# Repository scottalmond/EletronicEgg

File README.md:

# EletronicEgg
No-mess eletronic solution to the classical egg drop contest

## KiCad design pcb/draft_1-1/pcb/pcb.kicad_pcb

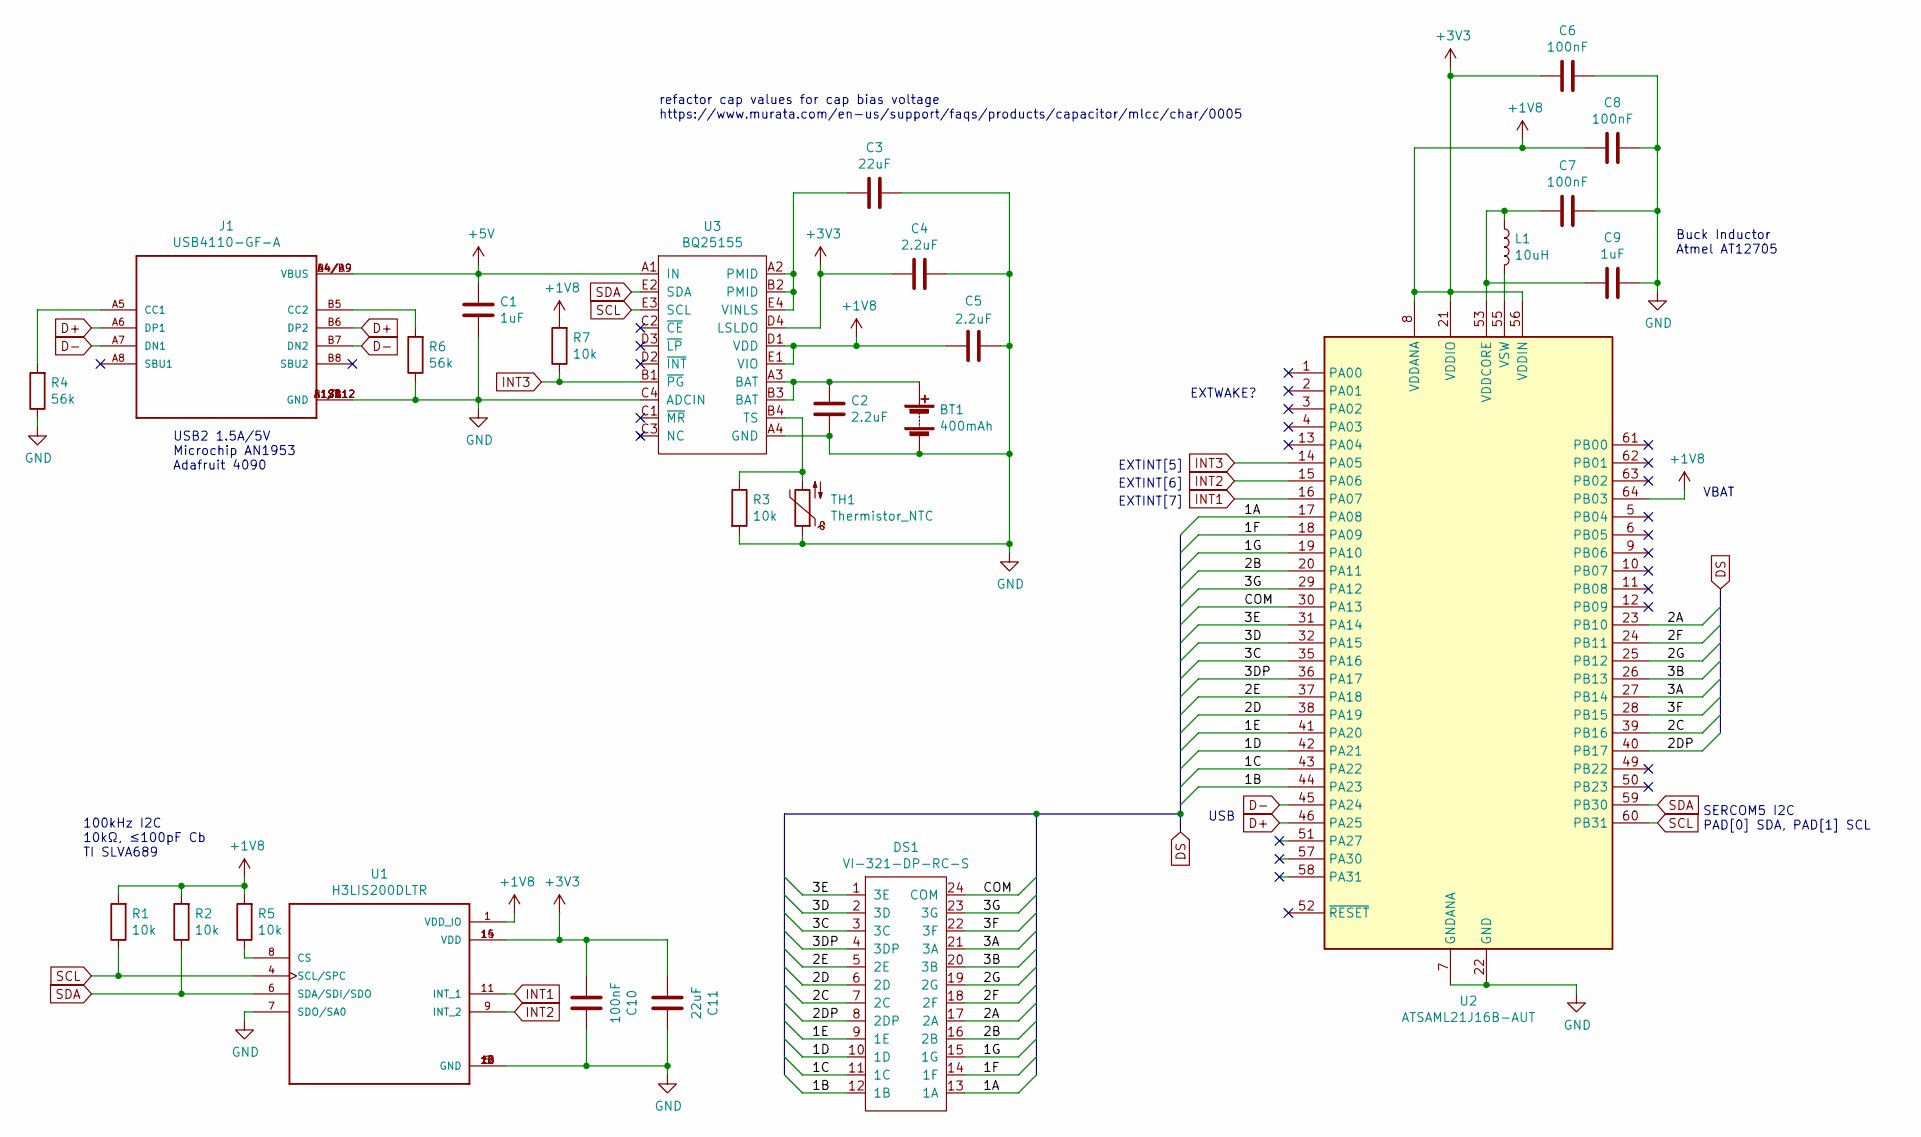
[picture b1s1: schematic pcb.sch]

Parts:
BT1: 400mAh; PinHeader_1x02_P2.54mm_Vertical
C1, C9: 1uF; C_0402_1005Metric
C2, C4, C5: 2.2uF; C_0402_1005Metric
C3, C11: 22uF; C_0805_2012Metric
C6, C7, C8, C10: 100nF; C_0402_1005Metric
DS1: VI-321-DP-RC-S
J1: USB4110-GF-A; GCT_USB4110-GF-A
L1: 10uH; L_0805_2012Metric
R1, R2, R3, R5, R7: 10k; R_0402_1005Metric
R4, R6: 56k; R_0402_1005Metric
TH1: Thermistor_NTC; R_0402_1005Metric
U1: H3LIS200DLTR; PQFN50P300X300X100-16N
U2: ATSAML21J16B-AUT; TQFP-64_10x10mm_P0.5mm
U3: BQ25155; BGA20C40P4X5_162X202X50

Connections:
+1V8: C4.1, C5.1, C6.1, C8.1, C10.2, C11.2, R1.2, R2.2, R5.2, R7.2, U1.1 (VDD_IO), U1.14 (VDD), U1.15 (VDD), U2.8 (VDDANA), U2.21 (VDDIO), U2.34 (VDDIO), U2.48 (VDDIO), U2.56 (VDDIN), U2.64 (PB03), U3.D1 (VDD), U3.D4 (LSLDO), U3.E1 (VIO)
+5V: C1.1, J1.A4/B9 (VBUS), J1.B4/A9 (VBUS), U3.A1 (IN)
/1A: DS1.13 (1A), U2.17 (PA08)
/1B: DS1.12 (1B), U2.44 (PA23)
/1C: DS1.11 (1C), U2.43 (PA22)
/1D: DS1.10 (1D), U2.42 (PA21)
/1E: DS1.9 (1E), U2.41 (PA20)
/1F: DS1.14 (1F), U2.18 (PA09)
/1G: DS1.15 (1G), U2.19 (PA10)
/2A: DS1.17 (2A), U2.23 (PB10)
/2B: DS1.16 (2B), U2.20 (PA11)
/2C: DS1.7 (2C), U2.39 (PB16)
/2D: DS1.6 (2D), U2.38 (PA19)
/2DP: DS1.8 (2DP), U2.40 (PB17)
/2E: DS1.5 (2E), U2.37 (PA18)
/2F: DS1.18 (2F), U2.24 (PB11)
/2G: DS1.19 (2G), U2.25 (PB12)
/3A: DS1.21 (3A), U2.27 (PB14)
/3B: DS1.20 (3B), U2.26 (PB13)
/3C: DS1.3 (3C), U2.35 (PA16)
/3D: DS1.2 (3D), U2.32 (PA15)
/3DP: DS1.4 (3DP), U2.36 (PA17)
/3E: DS1.1 (3E), U2.31 (PA14)
/3F: DS1.22 (3F), U2.28 (PB15)
/3G: DS1.23 (3G), U2.29 (PA12)
/COM: DS1.24 (COM), U2.30 (PA13)
D+: J1.A6 (DP1), J1.B6 (DP2), U2.46 (PA25)
D-: J1.A7 (DN1), J1.B7 (DN2), U2.45 (PA24)
GND: BT1.2 (-), C1.2, C2.2, C3.1, C4.2, C5.2, C6.2, C7.2, C8.2, C9.2, C10.1, C11.1, J1.A1/B12 (GND), J1.B1/A12 (GND), J1.S1 (GND), J1.S2 (GND), J1.S3 (GND), J1.S4 (GND), R3.2, R4.1, R6.1, TH1.1, U1.5 (GND), U1.7 (SDO/SA0), U1.10 (GND), U1.12 (GND), U1.13 (GND), U1.16 (GND), U2.7 (GNDANA), U2.22 (GND), U2.33 (GND), U2.47 (GND), U2.54 (GND), U3.A4 (GND), U3.C4 (ADCIN)
INT1: U1.11 (INT_1), U2.16 (PA07)
INT2: U1.9 (INT_2), U2.15 (PA06)
INT3: R7.1, U2.14 (PA05), U3.B1 (~PG)
unnamed: BT1.1 (+), C2.1, U3.A3 (BAT), U3.B3 (BAT)
unnamed: C3.2, U3.A2 (PMID), U3.B2 (PMID), U3.E4 (VINLS)
unnamed: C7.1, C9.1, L1.1, U2.53 (VDDCORE)
unnamed: J1.A5 (CC1), R4.2
unnamed: J1.B5 (CC2), R6.2
unnamed: L1.2, U2.55 (VSW)
unnamed: R3.1, TH1.2, U3.B4 (TS)
unnamed: R5.1, U1.8 (CS)
SCL: R1.1, U1.4 (SCL/SPC), U2.60 (PB31), U3.E3 (SCL)
SDA: R2.1, U1.6 (SDA/SDI/SDO), U2.59 (PB30), U3.E2 (SDA)

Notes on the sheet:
refactor cap values for cap bias voltage https://www.murata.com/en-us/support/faqs/products/capacitor/mlcc/char/0005
USB2 1.5A/5V Microchip AN1953 Adafruit 4090
USB
SERCOM5 I2C PAD[0] SDA, PAD[1] SCL
EXTINT[5]
EXTINT[6]
EXTINT[7]
100kHz I2C 10kΩ, ≤100pF Cb TI SLVA689
EXTWAKE?
VBAT
Buck Inductor Atmel AT12705

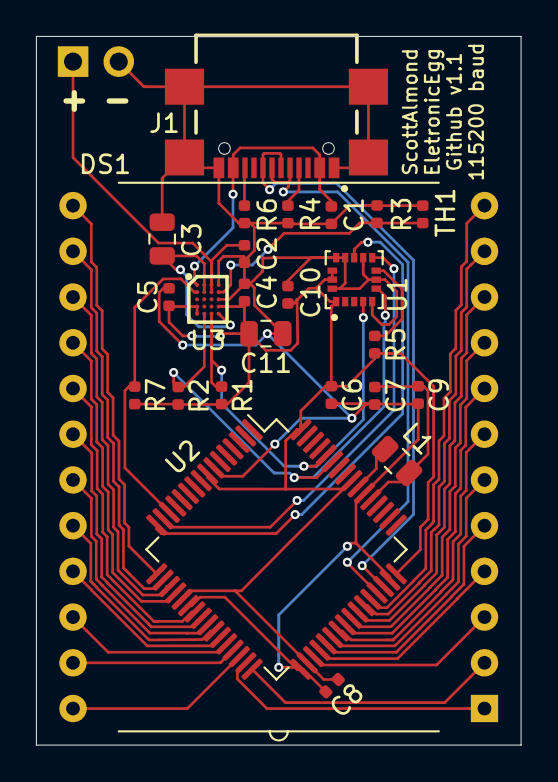
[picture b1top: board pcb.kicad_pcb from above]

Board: 2 copper layers, 26.9 x 39.4 mm, 26 parts (1 on the bottom side), 42 nets.

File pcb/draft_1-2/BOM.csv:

System Qty:,25,,,,,,,,,Price/quantity,,,,,,,,,,,,price per,,,,,,,,,ext price,,,,,,,,
Cost/System,$36.78,,,,,,,,,,,,,,,,,,,,,,,,,,,,,,,,,,,,,,
,,,,,,,,,,,,,,,,,,,,,,,,,,,,,,,,,,,,,,,
Description,Name,Pad,Component Qty/System,Component Qty to Order,Link,Alternate Link,,,,1,5,10,25,50,100,500,1000,,,,,1,5,10,25,50,100,500,1000,,1,5,10,25,50,100,500,1000,best value
400 mAh Battery,PRT-13851,BT1,1,25,https://www.digikey.com/product-detail/en/sparkfun-electroni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,https://www.sparkfun.com/products/13851,,,,4.95,,,,,,,,,,,25,4.95,4.95,4.95,4.95,4.95,4.95,4.95,4.95,,4.95,4.95,4.95,4.95,9.9,19.8,99,198,4.95
3 segment screen,VI-321-DP-RC-S,DS1,1,25,https://www.digikey.com/product-detail/en/varitronix/VI-321-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,,,,,6.3,,5.25,,,3.68,3.045,2.793,,,,25,6.3,6.3,5.25,5.25,5.25,3.68,3.045,2.793,,6.3,6.3,5.25,5.25,10.5,14.72,60.9,111.72,5.25
USB header,USB4110-GF-A,J1,1,10,https://www.digikey.com/product-detail/en/gct/USB4110-GF-A/2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,,,,,1.37,,1.25,1.69,1.12,1.067,0.88936,,,,,25,1.37,1.37,1.25,1.69,1.12,1.067,0.88936,0.88936,,1.37,1.37,1.25,1.69,2.24,4.268,17.7872,35.5744,1.25
200g accel,H3LIS200DLTR,U1,1,25,https://www.digikey.com/product-detail/en/stmicroelectronics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,,,,,7.34,,6.63,6.34,,5.49,4.78252,4.16543,,,,25,7.34,7.34,6.63,6.34,6.34,5.49,4.78252,4.16543,,7.34,7.34,6.63,6.34,12.68,21.96,95.6504,166.6172,6.34
SAML21J,ATSAML21J16B-AUT,U2,1,25,https://www.digikey.com/product-detail/en/microchip-technolo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,,,,,3.32,,,3.02,,2.73,,,,,,25,3.32,3.32,3.32,3.02,3.02,2.73,2.73,2.73,,3.32,3.32,3.32,3.02,6.04,10.92,54.6,109.2,3.02
PMIC/LDO,BQ25155YFPT,U3,1,25,https://www.digikey.com/product-detail/en/texas-instruments/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,,,,,3.31,,2.98,2.81,,2.31,,,,,,25,3.31,3.31,2.98,2.81,2.81,2.31,2.31,2.31,,3.31,3.31,2.98,2.81,5.62,9.24,46.2,92.4,2.81
1 uF 0805,CC0805KKX7R7BB105,"C1,C9",2,100,https://www.digikey.com/product-detail/en/yageo/CC0805KKX7R7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,,,,,0.18,,0.13,,,0.0611,,0.03544,,,,50,0.18,0.18,0.13,0.13,0.13,0.0611,0.0611,0.03544,,0.36,0.36,0.26,0.26,0.26,0.2444,1.222,1.4176,0.2444
2.2uF 0805,GCM21BR71E225KA73L,C2,1,25,https://www.digikey.com/product-detail/en/murata-electronics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,,,,,0.64,,0.453,,,0.298,0.22076,0.18764,,,,25,0.64,0.64,0.453,0.453,0.453,0.298,0.22076,0.18764,,0.64,0.64,0.453,0.453,0.906,1.192,4.4152,7.5056,0.453
10uF 0805,GRM21BR61E106KA73L,"C4,C5",2,50,https://www.digikey.com/product-detail/en/murata-electronics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,,,,,0.46,,0.322,,,0.193,0.14476,0.12224,,,,50,0.46,0.46,0.322,0.322,0.322,0.193,0.14476,0.12224,,0.92,0.92,0.644,0.644,0.644,0.772,2.8952,4.8896,0.644
22 uF 0805,CL21A226MQQNNNE,C3,1,25,https://www.digikey.com/product-detail/en/samsung-electro-me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,,,,,0.18,,0.121,,,0.061,0.04204,0.03719,,,,25,0.18,0.18,0.121,0.121,0.121,0.061,0.04204,0.03719,,0.18,0.18,0.121,0.121,0.242,0.244,0.8408,1.4876,0.121
100 nF 0805,08055C104KAT4A,"C6,C7,C8,C10",4,100,https://www.digikey.com/product-detail/en/avx-corporation/08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,,,,,0.11,,0.083,,,0.0372,0.02656,0.02087,,,,100,0.11,0.11,0.083,0.083,0.083,0.0372,0.02656,0.02087,,0.44,0.44,0.332,0.332,0.332,0.1488,0.5312,0.8348,0.1488
10 uH 0805,LBR2012T100K,L1,1,25,https://www.digikey.com/product-detail/en/taiyo-yuden/LBR201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,,,,,0.14,,0.13,,,0.086,0.07188,0.06038,,,,25,0.14,0.14,0.13,0.13,0.13,0.086,0.07188,0.06038,,0.14,0.14,0.13,0.13,0.26,0.344,1.4376,2.4152,0.13
10k 0805,RC0805FR-0710KL,"R1,R2,R3,R5,R7",5,100,https://www.digikey.com/product-detail/en/yageo/RC0805FR-071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,,,,,0.1,,0.04,,,0.0163,,0.00731,,,,125,0.1,0.1,0.04,0.04,0.04,0.0163,0.0163,0.00731,,0.5,0.5,0.2,0.2,0.2,0.0815,0.326,0.2924,0.0815
56k 0805,RC0805FR-0756KL,"R4,R6",2,100,https://www.digikey.com/product-detail/en/yageo/RC0805FR-075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,,,,,0.1,,0.04,,,0.0163,,0.00731,,,,50,0.1,0.1,0.04,0.04,0.04,0.0163,0.0163,0.00731,,0.2,0.2,0.08,0.08,0.08,0.0652,0.326,0.2924,0.0652
"10k Thermistor though hole, 1.3"" leads",NTCLE203E3103HB0,TH1,1,25,https://www.digikey.com/product-detail/en/vishay-bc-componen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,,,,,0.95,0.908,0.79,0.6944,0.5768,0.4913,0.4272,0.3738,,,,25,0.95,0.908,0.79,0.6944,0.5768,0.4913,0.4272,0.3738,,0.95,0.908,0.79,0.6944,1.1536,1.9652,8.544,14.952,0.6944
"Red LED 0603, 2mA 1.8V",TLMS1000-GS08,D1,1,25,https://www.digikey.com/product-detail/en/vishay-semiconduct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,,,,,0.49,,0.356,,,0.232,0.16688,0.13061,,,,25,0.49,0.49,0.356,0.356,0.356,0.232,0.16688,0.13061,,0.49,0.49,0.356,0.356,0.712,0.928,3.3376,5.2244,0.356
PCB,AllPCB 27 * 40 mm,,1,25,https://www.allpcb.com/online_pcb_quote.html,,,,,5,1,0.7,0.32,0.28,0.17,,,,,,25,5,1,0.7,0.32,0.28,0.17,0.17,0.17,,5,1,0.7,0.32,0.56,0.68,3.4,6.8,0.32
PCBA,"100 SMT, 11 BOM",,1,25,https://www.allpcb.com/pcba_quote.html,,,,,88.31,17.662,9.338,4.0544,3.1272,2.52,,,,,,25,88.31,17.662,9.338,4.0544,3.1272,2.52,2.52,2.52,,88.31,17.662,9.338,4.0544,6.2544,10.08,50.4,100.8,4.0544
Resin,2 oz/egg,,1,25,https://www.mcmaster.com/8644K58,,,,,35.71,7.142,3.571,,,,,,,,,25,35.71,7.142,3.571,3.571,3.571,3.571,3.571,3.571,,35.71,7.142,3.571,3.571,7.142,14.284,71.42,142.84,3.571
Silicone,8595K14,,1,25,https://www.mcmaster.com/8595K14,https://www.mcmaster.com/8595K15,,,,14.34,2.868,1.586,,,,,,,,,25,14.34,2.868,1.586,1.586,1.586,1.586,1.586,1.586,,14.34,2.868,1.586,1.586,3.172,6.344,31.72,63.44,1.586
Mold release,1409K52,,1,25,https://www.mcmaster.com/1409K52,,,,,8.67,1.734,0.867,0.6936,0.867,0.867,,,,,,25,8.67,1.734,0.867,0.6936,0.867,0.867,0.867,0.867,,8.67,1.734,0.867,0.6936,1.734,3.468,17.34,34.68,0.6936
Compressed Air,,,,,,,,,,,,,,,,,,,,,,,,,,,,,,,,,,,,,,,36.7833
Flux,,,,,,,,,,,,,,,,,,,,,,,,,,,,,,,,,,,,,,,
"100 mil headers, male",J2,,,,,,,,,,,,,,,,,,,,,,,,,,,,,,,,,,,,,,
,,,,,,,,,,,,,,,,,,,,,,,,,,,,,,,,,,,,,,,
,,,,,,,,,,,,,,,,,,,,,,,,1,180.83,,,,,,,,,,,,,,
,,,,,,,,,,,,,,,,,,,,,,,,5,58.201,,,,,,,,,,,,,,
,,,,,,,,,,,,,,,,,,,,,,,,10,41.6285,,,,,,,,,,,,,,
,,,,,,,,,,,,,,,,,,,,,,,,15,38.54833333,,,,,,,,,,,,,,
,,,,,,,,,,,,,,,,,,,,,,,,20,36.64,,,,,,,,,,,,,,
,,,,,,,,,,,,,,,,,,,,,,,,25,34.5146,,,,,,,,,,,,,,
,,,,,,,,,,,,,,,,,,,,,,,,30,34.44833333,,,,,,,,,,,,,,
,,,,,,,,,,,,,,,,,,,,,,,,35,34.41128571,,,,,,,,,,,,,,
,,,,,,,,,,,,,,,,,,,,,,,,40,34.2461,,,,,,,,,,,,,,
,,,,,,,,,,,,,,,,,,,,,,,,45,33.7786,,,,,,,,,,,,,,
,,,,,,,,,,,,,,,,,,,,,,,,50,33.2606,,,,,,,,,,,,,,
,,,,,,,,,,,,,,,,,,,,,,,,55,33.2606,,,,,,,,,,,,,,
,,,,,,,,,,,,,,,,,,,,,,,,60,33.2606,,,,,,,,,,,,,,
,,,,,,,,,,,,,,,,,,,,,,,,65,33.24213846,,,,,,,,,,,,,,
,,,,,,,,,,,,,,,,,,,,,,,,70,33.21631429,,,,,,,,,,,,,,
,,,,,,,,,,,,,,,,,,,,,,,,75,32.8486,,,,,,,,,,,,,,
,,,,,,,,,,,,,,,,,,,,,,,,80,32.5206,,,,,,,,,,,,,,
,,,,,,,,,,,,,,,,,,,,,,,,85,31.97634118,,,,,,,,,,,,,,
,,,,,,,,,,,,,,,,,,,,,,,,90,31.1634,,,10,~40,,,,,,,,,,
,,,,,,,,,,,,,,,,,,,,,,,,95,30.18182105,,,25,~35,,,,,,,,,,
,,,,,,,,,,,,,,,,,,,,,,,,100,29.2293,,,100,~30,,,,,,,,,,

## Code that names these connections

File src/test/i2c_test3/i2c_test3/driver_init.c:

/*
 * Code generated from Atmel Start.
 *
 * This file will be overwritten when reconfiguring your Atmel Start project.
 * Please copy examples or other code you want to keep to a separate file
 * to avoid losing it when reconfiguring.
 */

#include "driver_init.h"
#include <peripheral_clk_config.h>
#include <utils.h>
#include <hal_init.h>

struct i2c_m_sync_desc I2C_0;

void EXTERNAL_IRQ_0_init(void)
{
	hri_gclk_write_PCHCTRL_reg(GCLK, EIC_GCLK_ID, CONF_GCLK_EIC_SRC | (1 << GCLK_PCHCTRL_CHEN_Pos));
	hri_mclk_set_APBAMASK_EIC_bit(MCLK);

	// Set pin direction to input
	gpio_set_pin_direction(PA05, GPIO_DIRECTION_IN);

	gpio_set_pin_pull_mode(PA05,
	                       // <y> Pull configuration
	                       // <id> pad_pull_config
	                       // <GPIO_PULL_OFF"> Off
	                       // <GPIO_PULL_UP"> Pull-up
	                       // <GPIO_PULL_DOWN"> Pull-down
	                       GPIO_PULL_OFF);

	gpio_set_pin_function(PA05, PINMUX_PA05A_EIC_EXTINT5);

	// Set pin direction to input
	gpio_set_pin_direction(PA06, GPIO_DIRECTION_IN);

	gpio_set_pin_pull_mode(PA06,
	                       // <y> Pull configuration
	                       // <id> pad_pull_config
	                       // <GPIO_PULL_OFF"> Off
	                       // <GPIO_PULL_UP"> Pull-up
	                       // <GPIO_PULL_DOWN"> Pull-down
	                       GPIO_PULL_OFF);

	gpio_set_pin_function(PA06, PINMUX_PA06A_EIC_EXTINT6);

	// Set pin direction to input
	gpio_set_pin_direction(PA07, GPIO_DIRECTION_IN);

	gpio_set_pin_pull_mode(PA07,
	                       // <y> Pull configuration
	                       // <id> pad_pull_config
	                       // <GPIO_PULL_OFF"> Off
	                       // <GPIO_PULL_UP"> Pull-up
	                       // <GPIO_PULL_DOWN"> Pull-down
	                       GPIO_PULL_OFF);

	gpio_set_pin_function(PA07, PINMUX_PA07A_EIC_EXTINT7);

	ext_irq_init();
}

void I2C_0_PORT_init(void)
{

	gpio_set_pin_pull_mode(PB30,
	                       // <y> Pull configuration
	                       // <id> pad_pull_config
	                       // <GPIO_PULL_OFF"> Off
	                       // <GPIO_PULL_UP"> Pull-up
	                       // <GPIO_PULL_DOWN"> Pull-down
	                       GPIO_PULL_OFF);

	gpio_set_pin_function(PB30, PINMUX_PB30D_SERCOM5_PAD0);

	gpio_set_pin_pull_mode(PB31,
	                       // <y> Pull configuration
	                       // <id> pad_pull_config
	                       // <GPIO_PULL_OFF"> Off
	                       // <GPIO_PULL_UP"> Pull-up
	                       // <GPIO_PULL_DOWN"> Pull-down
	                       GPIO_PULL_OFF);

	gpio_set_pin_function(PB31, PINMUX_PB31D_SERCOM5_PAD1);
}

void I2C_0_CLOCK_init(void)
{
	hri_gclk_write_PCHCTRL_reg(GCLK, SERCOM5_GCLK_ID_CORE, CONF_GCLK_SERCOM5_CORE_SRC | (1 << GCLK_PCHCTRL_CHEN_Pos));
	hri_gclk_write_PCHCTRL_reg(GCLK, SERCOM5_GCLK_ID_SLOW, CONF_GCLK_SERCOM5_SLOW_SRC | (1 << GCLK_PCHCTRL_CHEN_Pos));

	hri_mclk_set_APBDMASK_SERCOM5_bit(MCLK);
}

void I2C_0_init(void)
{
	I2C_0_CLOCK_init();
	i2c_m_sync_init(&I2C_0, SERCOM5);
	I2C_0_PORT_init();
}

void system_init(void)
{
	init_mcu();

	// GPIO on PA08

	gpio_set_pin_level(DS_1A,
	                   // <y> Initial level
	                   // <id> pad_initial_level
	                   // <false"> Low
	                   // <true"> High
	                   false);

	// Set pin direction to output
	gpio_set_pin_direction(DS_1A, GPIO_DIRECTION_OUT);

	gpio_set_pin_function(DS_1A, GPIO_PIN_FUNCTION_OFF);

	// GPIO on PA09

	gpio_set_pin_level(DS_1F,
	                   // <y> Initial level
	                   // <id> pad_initial_level
	                   // <false"> Low
	                   // <true"> High
	                   false);

	// Set pin direction to output
	gpio_set_pin_direction(DS_1F, GPIO_DIRECTION_OUT);

	gpio_set_pin_function(DS_1F, GPIO_PIN_FUNCTION_OFF);

	// GPIO on PA10

	gpio_set_pin_level(DS_1G,
	                   // <y> Initial level
	                   // <id> pad_initial_level
	                   // <false"> Low
	                   // <true"> High
	                   false);

	// Set pin direction to output
	gpio_set_pin_direction(DS_1G, GPIO_DIRECTION_OUT);

	gpio_set_pin_function(DS_1G, GPIO_PIN_FUNCTION_OFF);

	// GPIO on PB22

	gpio_set_pin_level(LED_P,
	                   // <y> Initial level
	                   // <id> pad_initial_level
	                   // <false"> Low
	                   // <true"> High
	                   false);

	// Set pin direction to output
	gpio_set_pin_direction(LED_P, GPIO_DIRECTION_OUT);

	gpio_set_pin_function(LED_P, GPIO_PIN_FUNCTION_OFF);

	// GPIO on PB23

	gpio_set_pin_level(LED_N,
	                   // <y> Initial level
	                   // <id> pad_initial_level
	                   // <false"> Low
	                   // <true"> High
	                   false);

	// Set pin direction to output
	gpio_set_pin_direction(LED_N, GPIO_DIRECTION_OUT);

	gpio_set_pin_function(LED_N, GPIO_PIN_FUNCTION_OFF);

	EXTERNAL_IRQ_0_init();

	I2C_0_init();
}

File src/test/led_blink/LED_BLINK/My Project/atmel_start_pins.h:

/*
 * Code generated from Atmel Start.
 *
 * This file will be overwritten when reconfiguring your Atmel Start project.
 * Please copy examples or other code you want to keep to a separate file
 * to avoid losing it when reconfiguring.
 */
#ifndef ATMEL_START_PINS_H_INCLUDED
#define ATMEL_START_PINS_H_INCLUDED

#include <hal_gpio.h>

// SAML21 has 9 pin functions

#define GPIO_PIN_FUNCTION_A 0
#define GPIO_PIN_FUNCTION_B 1
#define GPIO_PIN_FUNCTION_C 2
#define GPIO_PIN_FUNCTION_D 3
#define GPIO_PIN_FUNCTION_E 4
#define GPIO_PIN_FUNCTION_F 5
#define GPIO_PIN_FUNCTION_G 6
#define GPIO_PIN_FUNCTION_H 7
#define GPIO_PIN_FUNCTION_I 8

#define PA05 GPIO(GPIO_PORTA, 5)
#define PA06 GPIO(GPIO_PORTA, 6)
#define PA07 GPIO(GPIO_PORTA, 7)
#define PA24 GPIO(GPIO_PORTA, 24)
#define PA25 GPIO(GPIO_PORTA, 25)
#define PB22 GPIO(GPIO_PORTB, 22)
#define PB23 GPIO(GPIO_PORTB, 23)
#define PB30 GPIO(GPIO_PORTB, 30)
#define PB31 GPIO(GPIO_PORTB, 31)

#endif // ATMEL_START_PINS_H_INCLUDED

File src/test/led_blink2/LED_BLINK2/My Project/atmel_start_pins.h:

/*
 * Code generated from Atmel Start.
 *
 * This file will be overwritten when reconfiguring your Atmel Start project.
 * Please copy examples or other code you want to keep to a separate file
 * to avoid losing it when reconfiguring.
 */
#ifndef ATMEL_START_PINS_H_INCLUDED
#define ATMEL_START_PINS_H_INCLUDED

#include <hal_gpio.h>

// SAML21 has 9 pin functions

#define GPIO_PIN_FUNCTION_A 0
#define GPIO_PIN_FUNCTION_B 1
#define GPIO_PIN_FUNCTION_C 2
#define GPIO_PIN_FUNCTION_D 3
#define GPIO_PIN_FUNCTION_E 4
#define GPIO_PIN_FUNCTION_F 5
#define GPIO_PIN_FUNCTION_G 6
#define GPIO_PIN_FUNCTION_H 7
#define GPIO_PIN_FUNCTION_I 8

#define PB22 GPIO(GPIO_PORTB, 22)
#define PB23 GPIO(GPIO_PORTB, 23)
#define PA23 GPIO(GPIO_PORTA, 23)
#define PA14 GPIO(GPIO_PORTA, 14)
#define PB30 GPIO(GPIO_PORTB, 30)
#define PB31 GPIO(GPIO_PORTB, 31)

#endif // ATMEL_START_PINS_H_INCLUDED

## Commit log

2019-12-10 concept draft
2019-12-31 schematic with SAML21G, will need to change to J for full pin compliement on 3.3V
2020-01-01 PRE-TRACE PLACEMENT CHECKPOINT
2020-01-03 attempt to route display
2020-01-03 bom cost estimate
2020-01-04 maximized squid traces
2020-01-04 added accel decouple caps
2020-01-05 candidate layout done
2020-01-05 as built
2020-01-10 bom cleanup
2020-01-10 led blink test
2020-01-11 screen works
2020-01-13 stencil
2020-01-17 as built protitype 1
2020-01-31 begin incorporating v1.2 changes
2020-02-04 organized silk screen and swd tp
2020-02-06 add example image to readme
2020-02-07 v1.2 draft
2020-02-07 v1.2 draft gerbers
2020-02-07 pcb as purchased
2020-02-08 pngs and bob as-ordered
2020-03-15 toggle PB30 SDA
2020-03-15 bq25155 id readback success
2020-03-15 write to BQ25155 success
2020-03-16 read/write established for both pmic and accel
2021-01-18 add 2*3 100 mil header to BOM
2021-04-16 change resistor for charging mode

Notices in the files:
pcb/draft_1-1/pcb/pcb.kicad_pcb:
License: CC BY 4.0
